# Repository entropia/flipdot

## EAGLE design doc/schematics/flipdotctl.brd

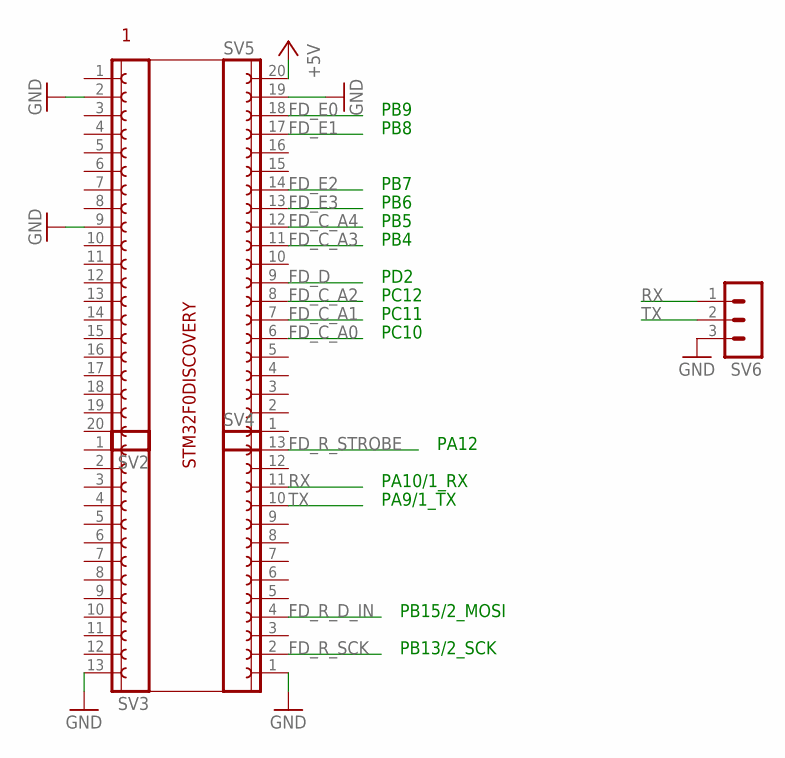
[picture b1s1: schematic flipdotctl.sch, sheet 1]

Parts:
SV2, SV5: FE20-1; FE20
SV3, SV4: FE13-1; FE13
SV6: MA03-1

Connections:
+5V: SV5.20; also elsewhere on the board
FD_C_A0: SV5.6; also elsewhere on the board
FD_C_A1: SV5.7; also elsewhere on the board
FD_C_A2: SV5.8; also elsewhere on the board
FD_C_A3: SV5.11; also elsewhere on the board
FD_C_A4: SV5.12; also elsewhere on the board
FD_D: SV5.9; also elsewhere on the board
FD_E0: SV5.18; also elsewhere on the board
FD_E1: SV5.17; also elsewhere on the board
FD_E2: SV5.14; also elsewhere on the board
FD_E3: SV5.13; also elsewhere on the board
FD_R_D_IN: SV4.4; also elsewhere on the board
FD_R_SCK: SV4.2; also elsewhere on the board
FD_R_STROBE: SV4.13; also elsewhere on the board
GND: SV2.2, SV2.9, SV3.13, SV4.1, SV5.19, SV6.3; also elsewhere on the board
RX: SV4.11, SV6.1
TX: SV4.10, SV6.2

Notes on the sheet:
STM32F0DISCOVERY
PB13/2_SCK
PB15/2_MOSI
PB9
PB8
PB7
PB6
PB5
PB4
PD2
PC12
PC11
PC10
PA12
PA9/1_TX
PA10/1_RX

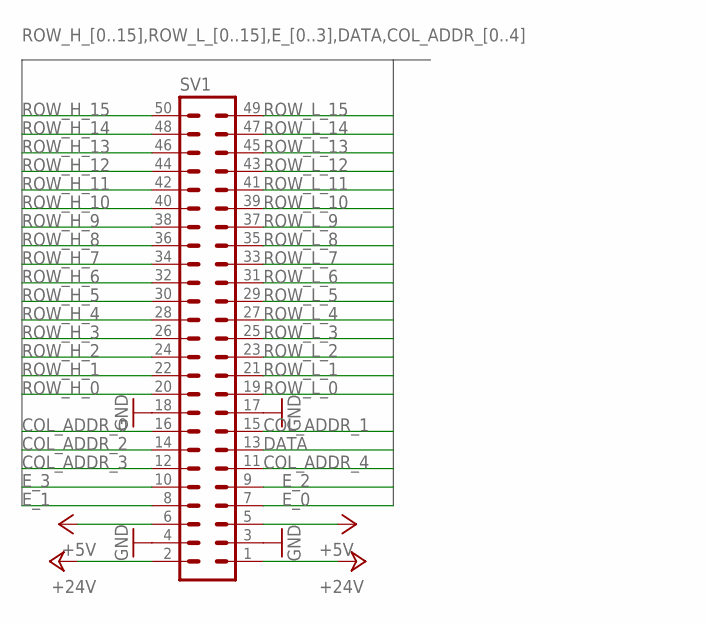
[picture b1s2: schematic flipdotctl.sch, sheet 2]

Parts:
SV1: ML50

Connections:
+5V: SV1.5, SV1.6; also elsewhere on the board
+24V: SV1.1, SV1.2; also elsewhere on the board
COL_ADDR_0: SV1.16; also elsewhere on the board
COL_ADDR_1: SV1.15; also elsewhere on the board
COL_ADDR_2: SV1.14; also elsewhere on the board
COL_ADDR_3: SV1.12; also elsewhere on the board
COL_ADDR_4: SV1.11; also elsewhere on the board
DATA: SV1.13; also elsewhere on the board
E_0: SV1.7; also elsewhere on the board
E_1: SV1.8; also elsewhere on the board
E_2: SV1.9; also elsewhere on the board
E_3: SV1.10; also elsewhere on the board
GND: SV1.3, SV1.4, SV1.17, SV1.18; also elsewhere on the board
ROW_H_0: SV1.20; also elsewhere on the board
ROW_H_1: SV1.22; also elsewhere on the board
ROW_H_2: SV1.24; also elsewhere on the board
ROW_H_3: SV1.26; also elsewhere on the board
ROW_H_4: SV1.28; also elsewhere on the board
ROW_H_5: SV1.30; also elsewhere on the board
ROW_H_6: SV1.32; also elsewhere on the board
ROW_H_7: SV1.34; also elsewhere on the board
ROW_H_8: SV1.36; also elsewhere on the board
ROW_H_9: SV1.38; also elsewhere on the board
ROW_H_10: SV1.40; also elsewhere on the board
ROW_H_11: SV1.42; also elsewhere on the board
ROW_H_12: SV1.44; also elsewhere on the board
ROW_H_13: SV1.46; also elsewhere on the board
ROW_H_14: SV1.48; also elsewhere on the board
ROW_H_15: SV1.50; also elsewhere on the board
ROW_L_0: SV1.19; also elsewhere on the board
ROW_L_1: SV1.21; also elsewhere on the board
ROW_L_2: SV1.23; also elsewhere on the board
ROW_L_3: SV1.25; also elsewhere on the board
ROW_L_4: SV1.27; also elsewhere on the board
ROW_L_5: SV1.29; also elsewhere on the board
ROW_L_6: SV1.31; also elsewhere on the board
ROW_L_7: SV1.33; also elsewhere on the board
ROW_L_8: SV1.35; also elsewhere on the board
ROW_L_9: SV1.37; also elsewhere on the board
ROW_L_10: SV1.39; also elsewhere on the board
ROW_L_11: SV1.41; also elsewhere on the board
ROW_L_12: SV1.43; also elsewhere on the board
ROW_L_13: SV1.45; also elsewhere on the board
ROW_L_14: SV1.47; also elsewhere on the board
ROW_L_15: SV1.49; also elsewhere on the board

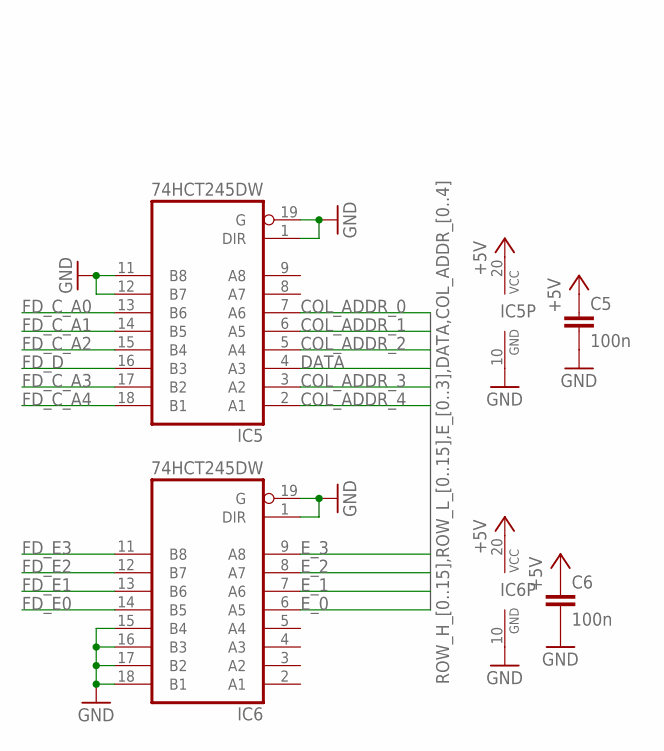
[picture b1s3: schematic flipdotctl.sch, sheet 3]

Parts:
C5, C6: 100n; C0603
IC5, IC6: 74HCT245DW; SO20W

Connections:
+5V: C5.1, C6.1, IC5.20 (VCC), IC6.20 (VCC); also elsewhere on the board
COL_ADDR_0: IC5.7 (A6); also elsewhere on the board
COL_ADDR_1: IC5.6 (A5); also elsewhere on the board
COL_ADDR_2: IC5.5 (A4); also elsewhere on the board
COL_ADDR_3: IC5.3 (A2); also elsewhere on the board
COL_ADDR_4: IC5.2 (A1); also elsewhere on the board
DATA: IC5.4 (A3); also elsewhere on the board
E_0: IC6.6 (A5); also elsewhere on the board
E_1: IC6.7 (A6); also elsewhere on the board
E_2: IC6.8 (A7); also elsewhere on the board
E_3: IC6.9 (A8); also elsewhere on the board
FD_C_A0: IC5.13 (B6); also elsewhere on the board
FD_C_A1: IC5.14 (B5); also elsewhere on the board
FD_C_A2: IC5.15 (B4); also elsewhere on the board
FD_C_A3: IC5.17 (B2); also elsewhere on the board
FD_C_A4: IC5.18 (B1); also elsewhere on the board
FD_D: IC5.16 (B3); also elsewhere on the board
FD_E0: IC6.14 (B5); also elsewhere on the board
FD_E1: IC6.13 (B6); also elsewhere on the board
FD_E2: IC6.12 (B7); also elsewhere on the board
FD_E3: IC6.11 (B8); also elsewhere on the board
GND: C5.2, C6.2, IC5.1 (DIR), IC5.10 (GND), IC5.11 (B8), IC5.12 (B7), IC5.19 (G), IC6.1 (DIR), IC6.10 (GND), IC6.15 (B4), IC6.16 (B3), IC6.17 (B2), IC6.18 (B1), IC6.19 (G); also elsewhere on the board

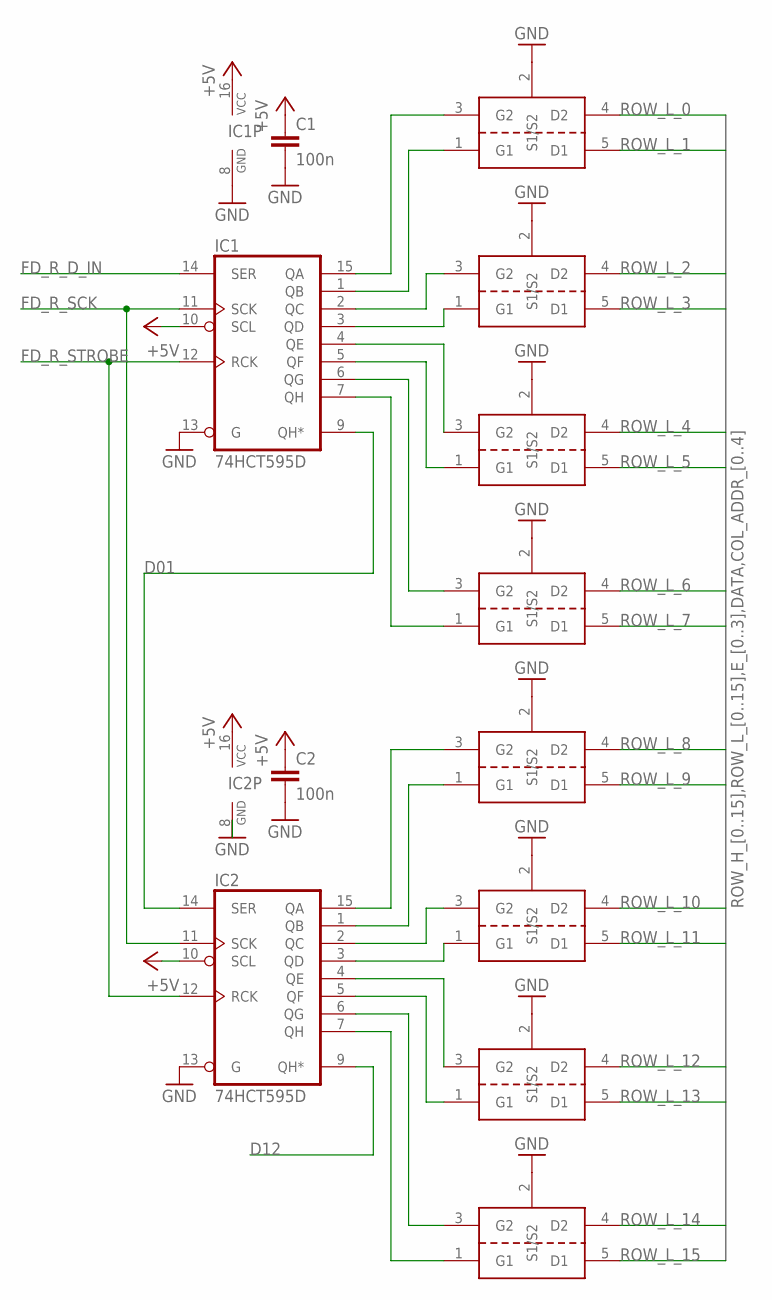
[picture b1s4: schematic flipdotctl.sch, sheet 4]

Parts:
C1, C2: 100n; C0603
IC1, IC2: 74HCT595D; SO16
U$1, U$2, U$3, U$4, U$5, U$6, U$7, U$8: QS5K2; SOT23-5L

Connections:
+5V: C1.1, C2.1, IC1.10 (SCL), IC1.16 (VCC), IC2.10 (SCL), IC2.16 (VCC); also elsewhere on the board
D01: IC1.9 (QH*), IC2.14 (SER)
D12: IC2.9 (QH*); also elsewhere on the board
FD_R_D_IN: IC1.14 (SER); also elsewhere on the board
FD_R_SCK: IC1.11 (SCK), IC2.11 (SCK); also elsewhere on the board
FD_R_STROBE: IC1.12 (RCK), IC2.12 (RCK); also elsewhere on the board
GND: C1.2, C2.2, IC1.8 (GND), IC1.13 (G), IC2.8 (GND), IC2.13 (G), U$1.2 (S1/S2), U$2.2 (S1/S2), U$3.2 (S1/S2), U$4.2 (S1/S2), U$5.2 (S1/S2), U$6.2 (S1/S2), U$7.2 (S1/S2), U$8.2 (S1/S2); also elsewhere on the board
L_0: IC1.15 (QA), U$1.3 (G2)
L_1: IC1.1 (QB), U$1.1 (G1)
L_2: IC1.2 (QC), U$2.3 (G2)
L_3: IC1.3 (QD), U$2.1 (G1)
L_4: IC1.4 (QE), U$3.3 (G2)
L_5: IC1.5 (QF), U$3.1 (G1)
L_6: IC1.6 (QG), U$4.3 (G2)
L_7: IC1.7 (QH), U$4.1 (G1)
L_8: IC2.15 (QA), U$5.3 (G2)
L_9: IC2.1 (QB), U$5.1 (G1)
L_10: IC2.2 (QC), U$6.3 (G2)
L_11: IC2.3 (QD), U$6.1 (G1)
L_12: IC2.4 (QE), U$7.3 (G2)
L_13: IC2.5 (QF), U$7.1 (G1)
L_14: IC2.6 (QG), U$8.3 (G2)
L_15: IC2.7 (QH), U$8.1 (G1)
ROW_L_0: U$1.4 (D2); also elsewhere on the board
ROW_L_1: U$1.5 (D1); also elsewhere on the board
ROW_L_2: U$2.4 (D2); also elsewhere on the board
ROW_L_3: U$2.5 (D1); also elsewhere on the board
ROW_L_4: U$3.4 (D2); also elsewhere on the board
ROW_L_5: U$3.5 (D1); also elsewhere on the board
ROW_L_6: U$4.4 (D2); also elsewhere on the board
ROW_L_7: U$4.5 (D1); also elsewhere on the board
ROW_L_8: U$5.4 (D2); also elsewhere on the board
ROW_L_9: U$5.5 (D1); also elsewhere on the board
ROW_L_10: U$6.4 (D2); also elsewhere on the board
ROW_L_11: U$6.5 (D1); also elsewhere on the board
ROW_L_12: U$7.4 (D2); also elsewhere on the board
ROW_L_13: U$7.5 (D1); also elsewhere on the board
ROW_L_14: U$8.4 (D2); also elsewhere on the board
ROW_L_15: U$8.5 (D1); also elsewhere on the board

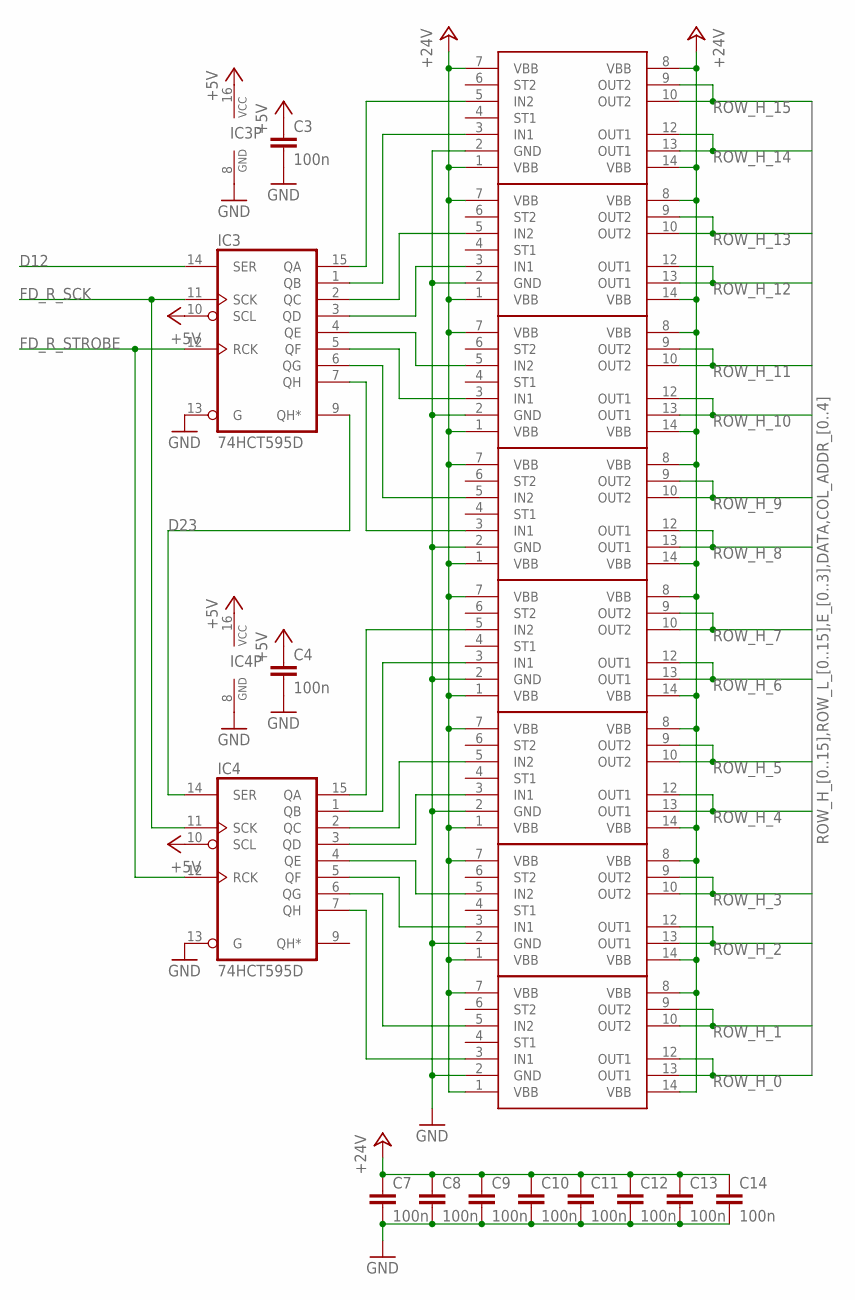
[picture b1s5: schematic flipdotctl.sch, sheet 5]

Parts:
C3, C4, C7, C8, C9, C10, C11, C12, C13, C14: 100n; C0603
IC3, IC4: 74HCT595D; SO16
U$9, U$10, U$11, U$12, U$13, U$14, U$15, U$16: BTS5210G; SO-14

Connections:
+5V: C3.1, C4.1, IC3.10 (SCL), IC3.16 (VCC), IC4.10 (SCL), IC4.16 (VCC); also elsewhere on the board
+24V: C7.1, C8.1, C9.1, C10.1, C11.1, C12.1, C13.1, C14.1, U$9.1 (VBB), U$9.7 (VBB), U$9.8 (VBB), U$9.14 (VBB), U$10.1 (VBB), U$10.7 (VBB), U$10.8 (VBB), U$10.14 (VBB), U$11.1 (VBB), U$11.7 (VBB), U$11.8 (VBB), U$11.14 (VBB), U$12.1 (VBB), U$12.7 (VBB), U$12.8 (VBB), U$12.14 (VBB), U$13.1 (VBB), U$13.7 (VBB), U$13.8 (VBB), U$13.14 (VBB), U$14.1 (VBB), U$14.7 (VBB), U$14.8 (VBB), U$14.14 (VBB), U$15.1 (VBB), U$15.7 (VBB), U$15.8 (VBB), U$15.14 (VBB), U$16.1 (VBB), U$16.7 (VBB), U$16.8 (VBB), U$16.14 (VBB); also elsewhere on the board
D12: IC3.14 (SER); also elsewhere on the board
D23: IC3.9 (QH*), IC4.14 (SER)
FD_R_SCK: IC3.11 (SCK), IC4.11 (SCK); also elsewhere on the board
FD_R_STROBE: IC3.12 (RCK), IC4.12 (RCK); also elsewhere on the board
GND: C3.2, C4.2, C7.2, C8.2, C9.2, C10.2, C11.2, C12.2, C13.2, C14.2, IC3.8 (GND), IC3.13 (G), IC4.8 (GND), IC4.13 (G), U$9.2 (GND), U$10.2 (GND), U$11.2 (GND), U$12.2 (GND), U$13.2 (GND), U$14.2 (GND), U$15.2 (GND), U$16.2 (GND); also elsewhere on the board
H_0: IC4.7 (QH), U$9.3 (IN1)
H_1: IC4.6 (QG), U$9.5 (IN2)
H_2: IC4.5 (QF), U$10.3 (IN1)
H_3: IC4.4 (QE), U$10.5 (IN2)
H_4: IC4.3 (QD), U$11.3 (IN1)
H_5: IC4.2 (QC), U$11.5 (IN2)
H_6: IC4.1 (QB), U$12.3 (IN1)
H_7: IC4.15 (QA), U$12.5 (IN2)
H_8: IC3.7 (QH), U$13.3 (IN1)
H_9: IC3.6 (QG), U$13.5 (IN2)
H_10: IC3.5 (QF), U$14.3 (IN1)
H_11: IC3.4 (QE), U$14.5 (IN2)
H_12: IC3.3 (QD), U$15.3 (IN1)
H_13: IC3.2 (QC), U$15.5 (IN2)
H_14: IC3.1 (QB), U$16.3 (IN1)
H_15: IC3.15 (QA), U$16.5 (IN2)
ROW_H_0: U$9.12 (OUT1), U$9.13 (OUT1); also elsewhere on the board
ROW_H_1: U$9.9 (OUT2), U$9.10 (OUT2); also elsewhere on the board
ROW_H_2: U$10.12 (OUT1), U$10.13 (OUT1); also elsewhere on the board
ROW_H_3: U$10.9 (OUT2), U$10.10 (OUT2); also elsewhere on the board
ROW_H_4: U$11.12 (OUT1), U$11.13 (OUT1); also elsewhere on the board
ROW_H_5: U$11.9 (OUT2), U$11.10 (OUT2); also elsewhere on the board
ROW_H_6: U$12.12 (OUT1), U$12.13 (OUT1); also elsewhere on the board
ROW_H_7: U$12.9 (OUT2), U$12.10 (OUT2); also elsewhere on the board
ROW_H_8: U$13.12 (OUT1), U$13.13 (OUT1); also elsewhere on the board
ROW_H_9: U$13.9 (OUT2), U$13.10 (OUT2); also elsewhere on the board
ROW_H_10: U$14.12 (OUT1), U$14.13 (OUT1); also elsewhere on the board
ROW_H_11: U$14.9 (OUT2), U$14.10 (OUT2); also elsewhere on the board
ROW_H_12: U$15.12 (OUT1), U$15.13 (OUT1); also elsewhere on the board
ROW_H_13: U$15.9 (OUT2), U$15.10 (OUT2); also elsewhere on the board
ROW_H_14: U$16.12 (OUT1), U$16.13 (OUT1); also elsewhere on the board
ROW_H_15: U$16.9 (OUT2), U$16.10 (OUT2); also elsewhere on the board

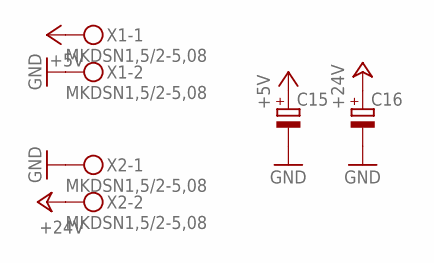
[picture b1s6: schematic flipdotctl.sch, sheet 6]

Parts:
C15, C16: CPOL-EUE2.5-6; E2,5-6
X1, X2: MKDSN1,5/2-5,08

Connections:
+5V: C15.+, X1.1; also elsewhere on the board
+24V: C16.+, X2.2; also elsewhere on the board
GND: C15.-, C16.-, X1.2, X2.1; also elsewhere on the board

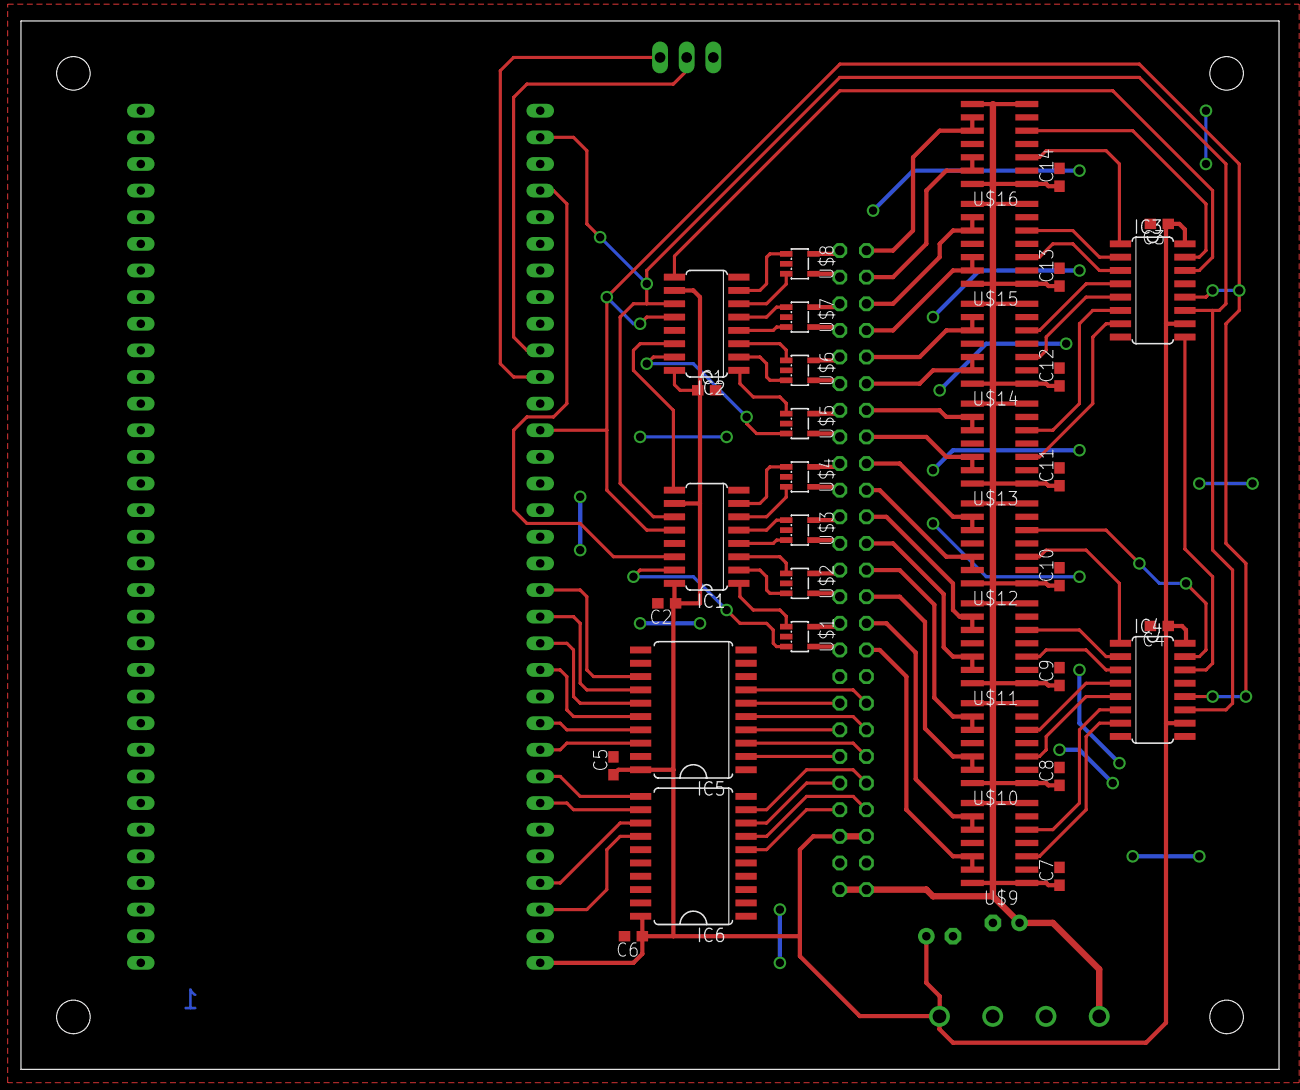
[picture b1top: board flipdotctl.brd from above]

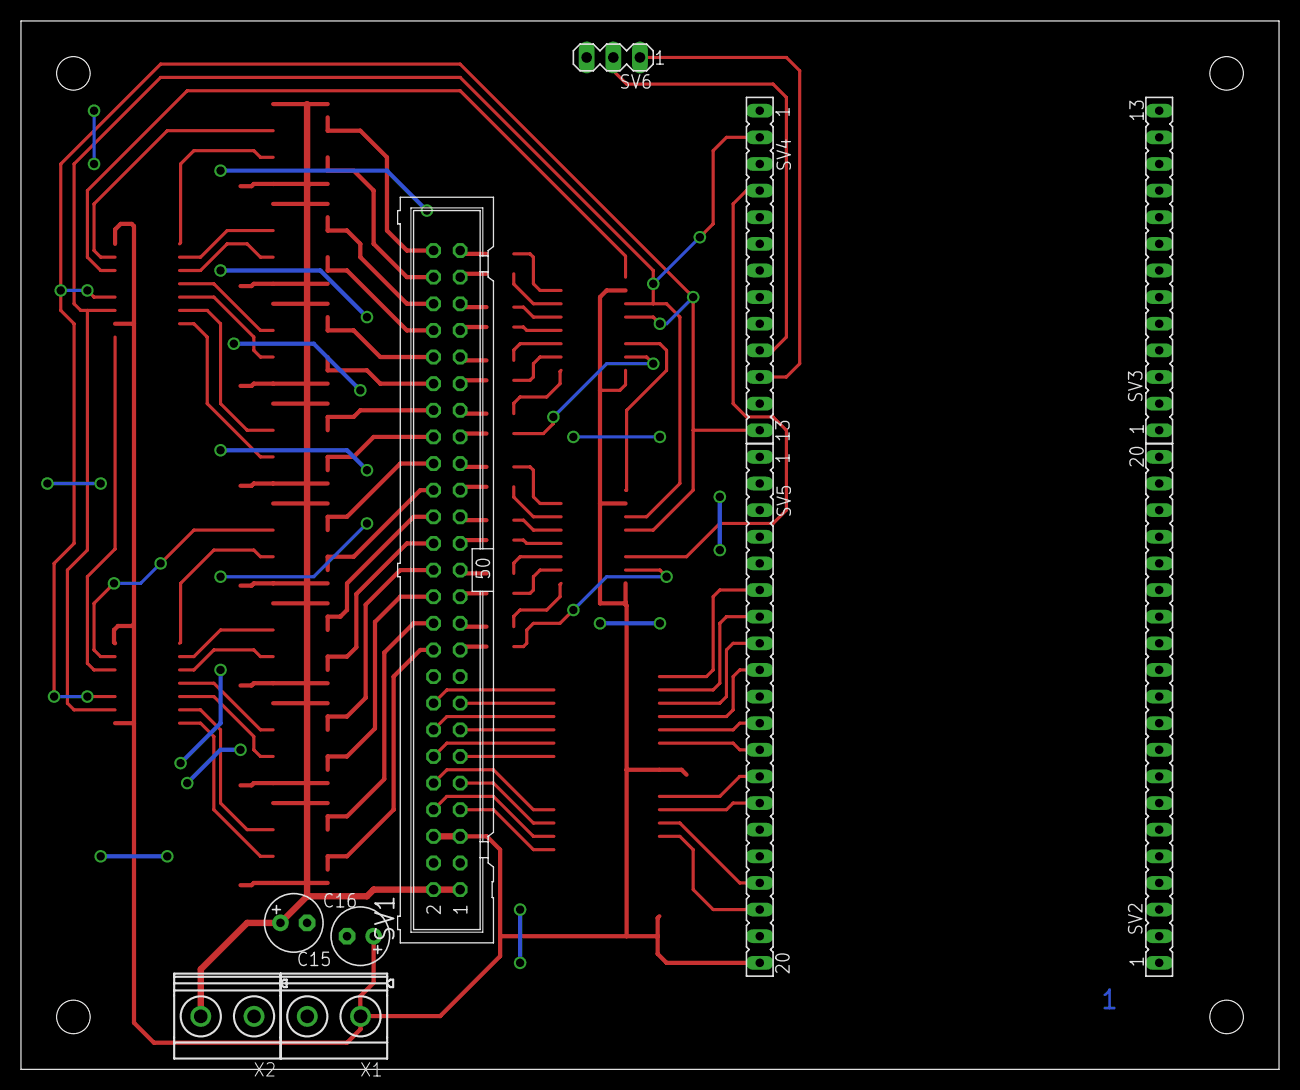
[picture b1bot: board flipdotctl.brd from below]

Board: 2 copper layers, 120.0 x 100.0 mm, 46 parts (10 on the bottom side), 95 nets.

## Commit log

2013-04-27 add schematics
2013-08-07 add firmware
